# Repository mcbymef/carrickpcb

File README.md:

Contains Eagle projects for independent study PCB

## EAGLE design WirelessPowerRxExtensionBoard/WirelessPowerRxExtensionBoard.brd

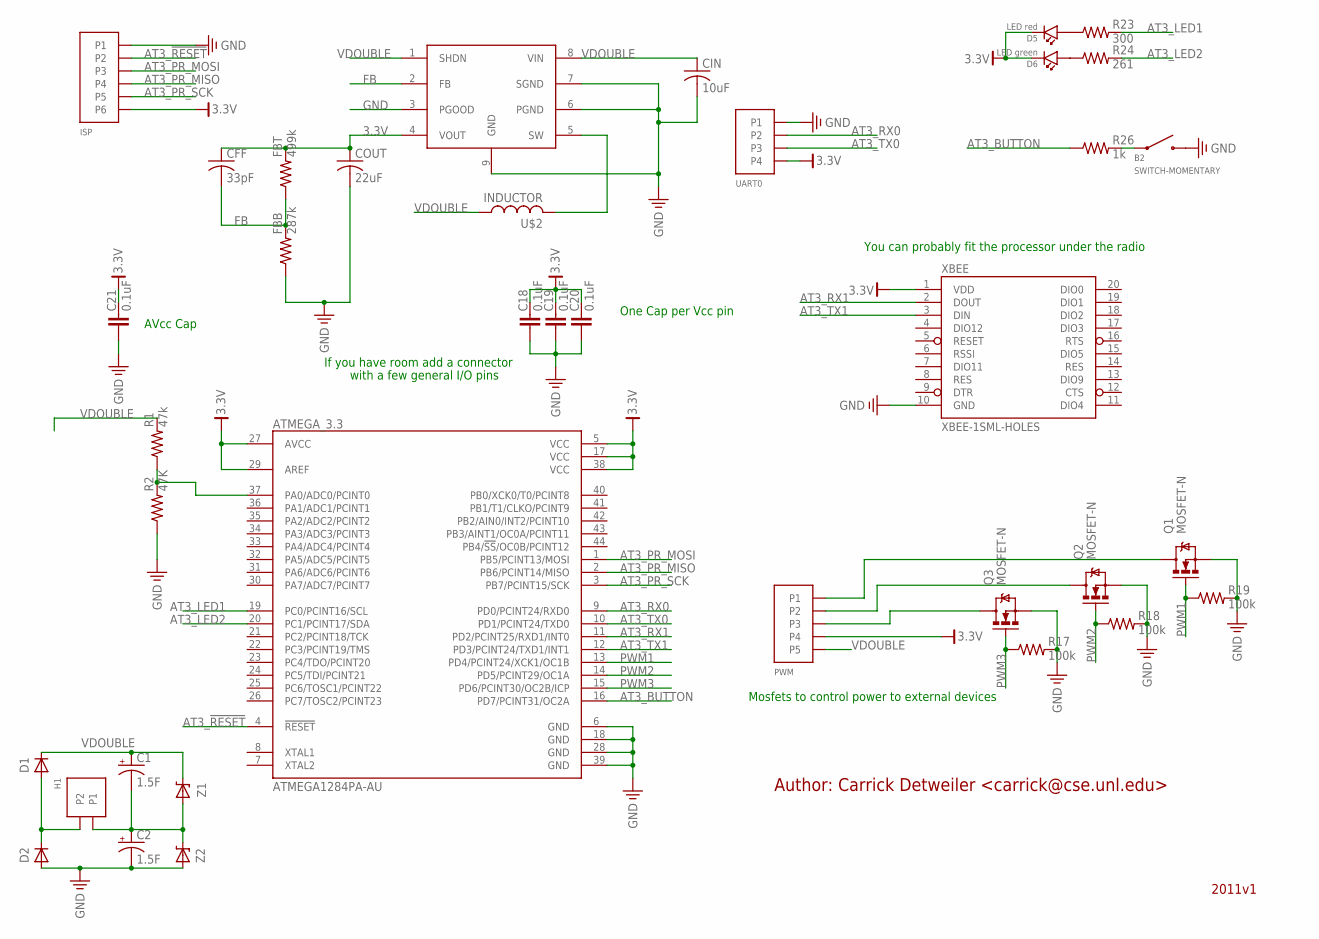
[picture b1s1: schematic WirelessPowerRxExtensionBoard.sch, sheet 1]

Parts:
ATMEGA_3.3: ATMEGA1284PA-AU; AT_TQFP-44
B2: SWITCH-MOMENTARY; SWITCH-MOMENTARY-PTS635-SMD
C1, C2: 1.5F; E5-10,5
C18, C19, C20, C21: 0.1uF; C0603
CFF: 33pF; C0201
CIN: 10uF; C0805
COUT: 22uF; C0805
D1, D2: DIODE; DO-214AB
D5: LED red; LED0603; DIGIKEY 160-1181-1-ND
D6: LED green; LED0603; DIGIKEY 160-1435-1-ND
FBB: 287k; R0603
FBT: 499k; R0603
H1: DF3-2
ISP: DF3-6
PWM: DF3-5
Q1, Q2, Q3: MOSFET-N; SOT-23
R1: 47k; R0603
R2: 47K; R0603
R17, R18, R19: 100k; R0603
R23: 300; R0603
R24: 261; R0603
R26: 1k; R0603
U$1: STEPUPCONVERTER; LTC3528/LTC3528B
U$2: INDUCTOR; WE-TPC-M
UART0: DF3-4
XBEE: XBEE-1SML-HOLES; XBEE-SML-HOLES
Z1, Z2: ZENERDIODE; SOD-123

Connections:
3.3V: ATMEGA_3.3.5 (VCC), ATMEGA_3.3.17 (VCC), ATMEGA_3.3.27 (AVCC), ATMEGA_3.3.29 (AREF), ATMEGA_3.3.38 (VCC), C18.P$2, C19.P$2, C20.P$2, C21.P$2, CFF.1, COUT.1, D5.P$2, D6.P$2, FBT.P$2 (2), ISP.P$6 (P6), PWM.P$4 (P4), U$1.4 (VOUT), UART0.P$4 (P4), XBEE.1 (VDD)
AT3_!RESET!: ATMEGA_3.3.4 (!RESET!), ISP.P$2 (P2)
AT3_BUTTON: ATMEGA_3.3.16 (PD7/PCINT31/OC2A), R26.P$1 (1)
AT3_LED1: ATMEGA_3.3.19 (PC0/PCINT16/SCL), R23.P$2 (2)
AT3_LED2: ATMEGA_3.3.20 (PC1/PCINT17/SDA), R24.P$2 (2)
AT3_PR_MISO: ATMEGA_3.3.2 (PB6/PCINT14/MISO), ISP.P$4 (P4)
AT3_PR_MOSI: ATMEGA_3.3.1 (PB5/PCINT13/MOSI), ISP.P$3 (P3)
AT3_PR_SCK: ATMEGA_3.3.3 (PB7/PCINT15/SCK), ISP.P$5 (P5)
AT3_RX0: ATMEGA_3.3.9 (PD0/PCINT24/RXD0), UART0.P$2 (P2)
AT3_RX1: ATMEGA_3.3.11 (PD2/PCINT25/RXD1/INT0), XBEE.2 (DOUT)
AT3_TX0: ATMEGA_3.3.10 (PD1/PCINT24/TXD0), UART0.P$3 (P3)
AT3_TX1: ATMEGA_3.3.12 (PD3/PCINT24/TXD1/INT1), XBEE.3 (DIN)
FB: CFF.2, FBB.P$2 (2), FBT.P$1 (1), U$1.2 (FB)
GND: ATMEGA_3.3.6 (GND), ATMEGA_3.3.18 (GND), ATMEGA_3.3.28 (GND), ATMEGA_3.3.39 (GND), B2.P$2, C2.-, C18.P$1, C19.P$1, C20.P$1, C21.P$1, CIN.2, COUT.2, D2.P$2 (A), FBB.P$1 (1), ISP.P$1 (P1), Q1.2 (S), Q2.2 (S), Q3.2 (S), R2.P$1 (1), R17.P$2 (2), R18.P$2 (2), R19.P$2 (2), U$1.3 (PGOOD), U$1.6 (PGND), U$1.7 (SGND), U$1.9 (GND), UART0.P$1 (P1), XBEE.10 (GND), Z2.P$2 (A)
unnamed: D1.P$2 (A), D2.P$1 (C), H1.P$2 (P2)
unnamed: ATMEGA_3.3.37 (PA0/ADC0/PCINT0), R1.P$1 (1), R2.P$2 (2)
unnamed: C1.-, C2.+, H1.P$1 (P1), Z1.P$2 (A), Z2.P$1 (C)
unnamed: PWM.P$3 (P3), Q3.3 (D)
unnamed: PWM.P$2 (P2), Q2.3 (D)
unnamed: B2.P$1, R26.P$2 (2)
unnamed: PWM.P$1 (P1), Q1.3 (D)
unnamed: D5.P$1, R23.P$1 (1)
unnamed: D6.P$1, R24.P$1 (1)
PWM1: ATMEGA_3.3.13 (PD4/PCINT24/XCK1/OC1B), Q1.1 (G), R19.P$1 (1)
PWM2: ATMEGA_3.3.14 (PD5/PCINT29/OC1A), Q2.1 (G), R18.P$1 (1)
PWM3: ATMEGA_3.3.15 (PD6/PCINT30/OC2B/ICP), Q3.1 (G), R17.P$1 (1)
SW: U$1.5 (SW), U$2.P$2 (2)
VDOUBLE: C1.+, CIN.1, D1.P$1 (C), PWM.P$5 (P5), R1.P$2 (2), U$1.1 (SHDN), U$1.8 (VIN), U$2.P$1 (1), Z1.P$1 (C)

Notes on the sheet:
Author: Carrick Detweiler <carrick@cse.unl.edu>
2011v1
One Cap per Vcc pin
AVcc Cap
If you have room add a connector
with a few general I/O pins
You can probably fit the processor under the radio
Mosfets to control power to external devices

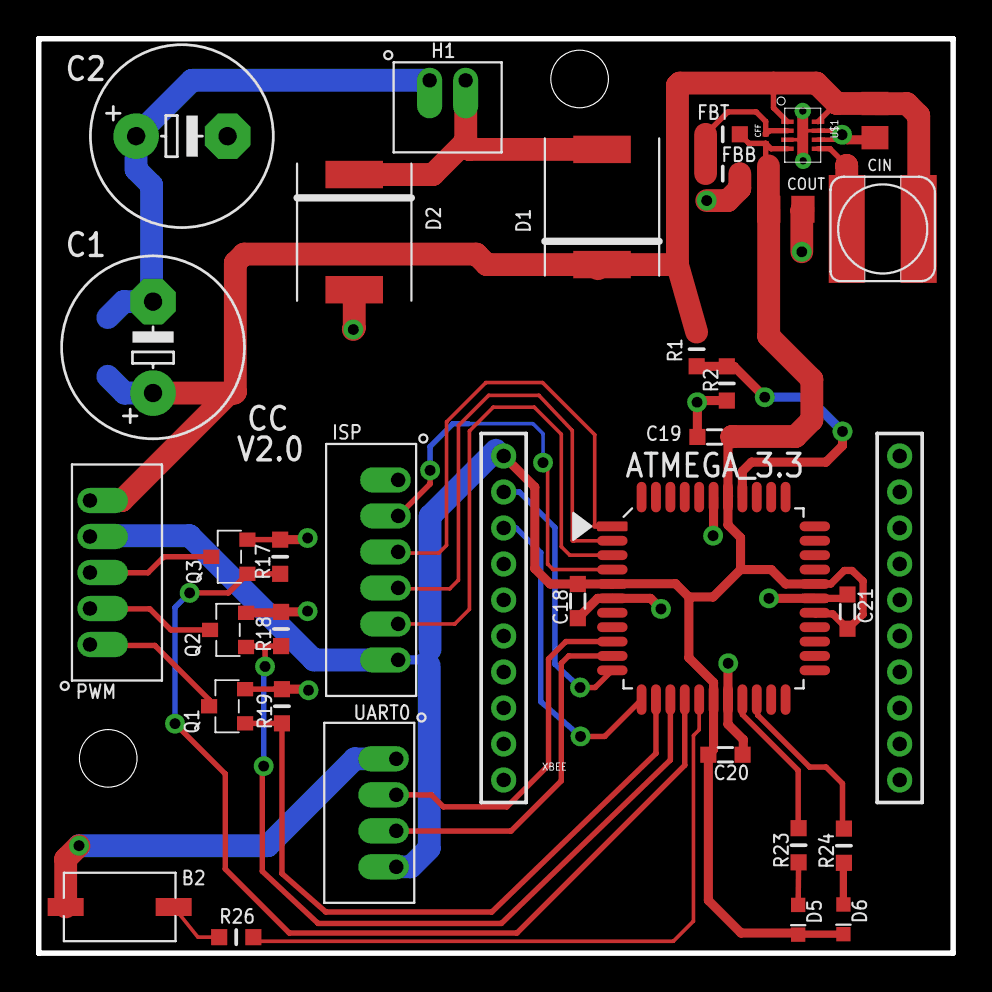
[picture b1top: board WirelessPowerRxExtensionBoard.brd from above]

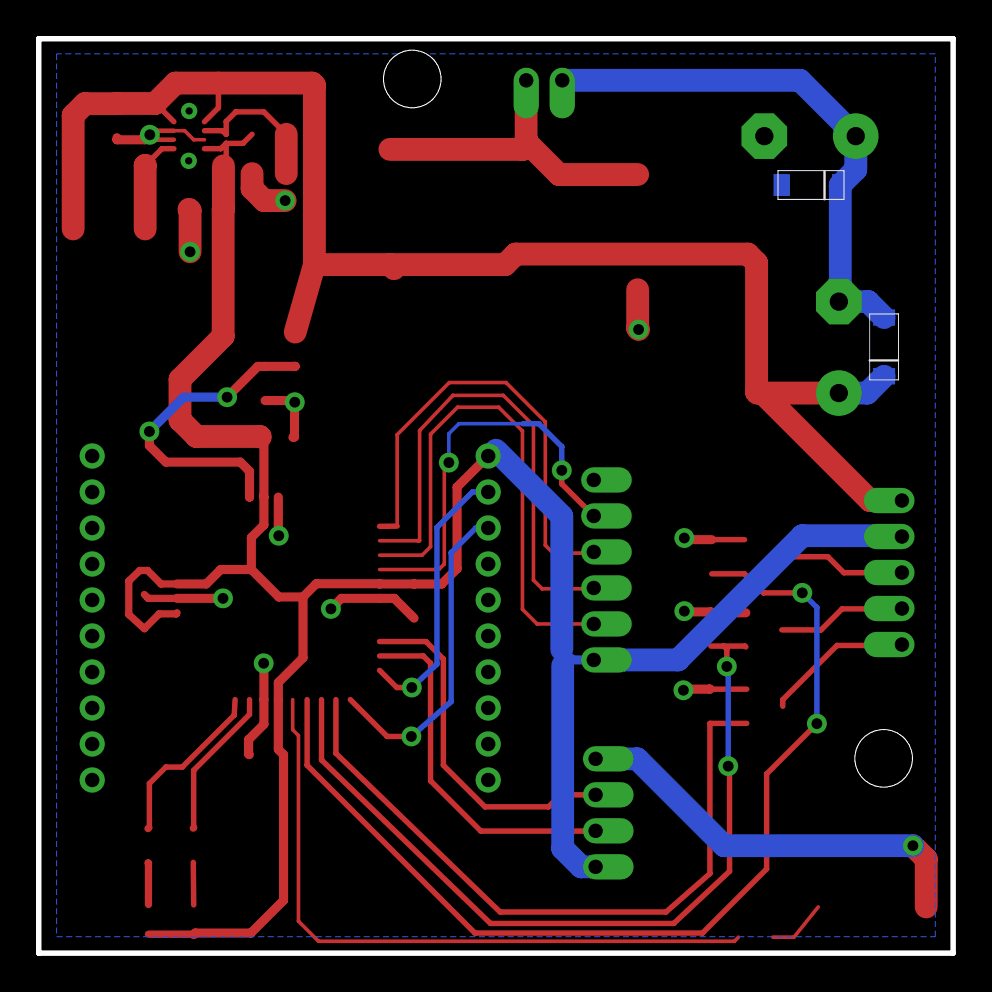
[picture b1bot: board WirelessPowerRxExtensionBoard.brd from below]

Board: 2 copper layers, 50.8 x 50.8 mm, 37 parts (2 on the bottom side), 28 nets.

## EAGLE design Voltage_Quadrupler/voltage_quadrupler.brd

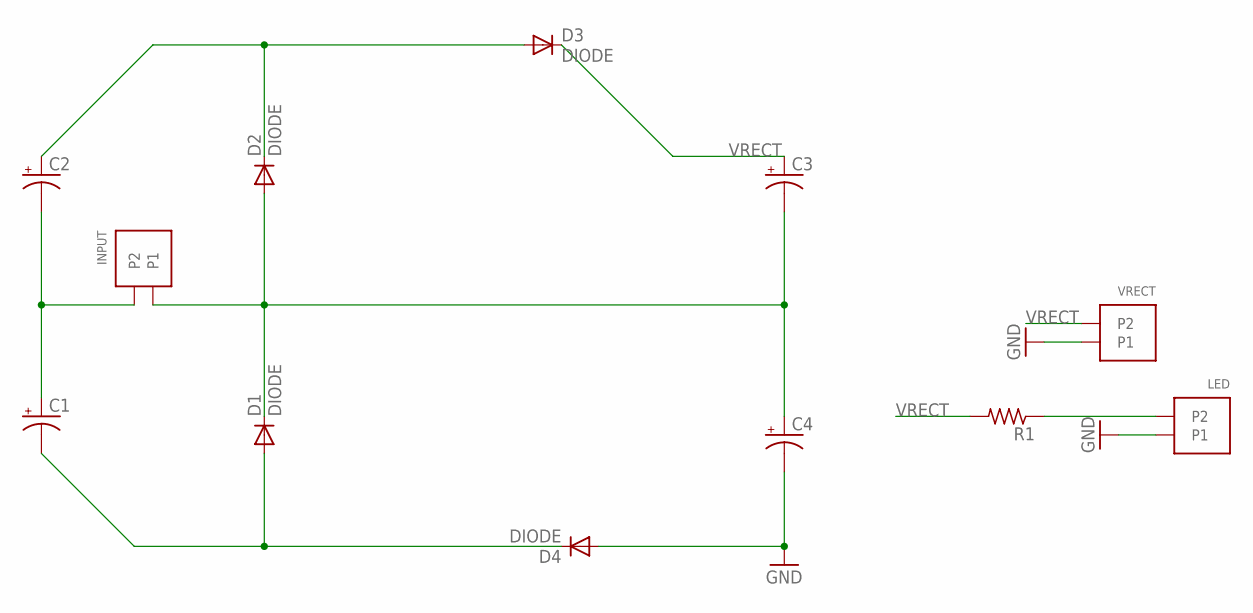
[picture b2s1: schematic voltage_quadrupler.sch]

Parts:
C1, C2, C3, C4: CPOL-USE7.5-18; E7,5-18
D1, D2, D3, D4: DIODE; DO-214AB
INPUT: DF3-2
LED: DF3-2
R1: R-US_0207/7; 0207/7
VRECT: DF3-2

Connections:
GND: C4.-, D4.P$2 (A), LED.P$1 (P1), VRECT.P$1 (P1)
unnamed: C3.-, C4.+, D1.P$1 (C), D2.P$2 (A), INPUT.P$1 (P1)
unnamed: C2.+, D2.P$1 (C), D3.P$2 (A)
unnamed: C1.+, C2.-, INPUT.P$2 (P2)
unnamed: C1.-, D1.P$2 (A), D4.P$1 (C)
unnamed: LED.P$2 (P2), R1.1
VRECT: C3.+, D3.P$1 (C), R1.2, VRECT.P$2 (P2)

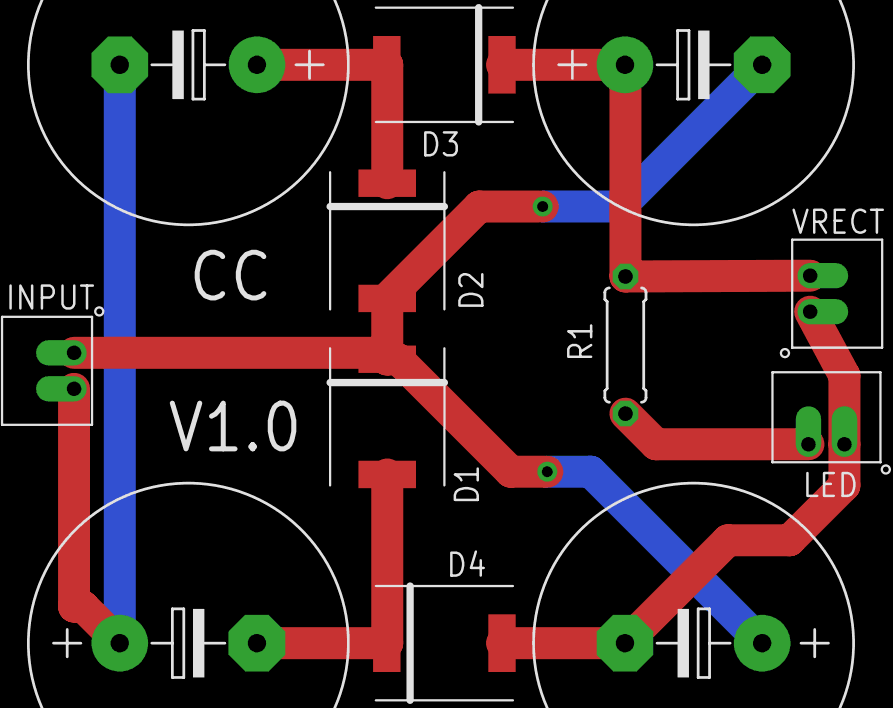
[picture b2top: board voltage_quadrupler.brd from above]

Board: 2 copper layers, 12 parts (0 on the bottom side), 7 nets.

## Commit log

2013-04-01 Adding Wireless Power Rx Extension Board Schematic
2013-04-03 Adding My Library
2013-04-03 Integrated MCU with Voltage Doubler and Regulator
    Board still needs to be routed, verify schematic with Carrick as well.
2013-04-05 Finished Schematic for Wireless Power Rx Extension Board
    Also updated crawford library to include zener diode
2013-04-07 Lots of Routing progress
    Routing!
2013-04-08 Finished First Pass at Routing
    still need to add vias to ground for voltage regulator
2013-04-10 Updated Routing
    Re-routed power section with much larger traces and added ground plane.
    Moved MCU resistors and caps under the radio but they still need to be
    re-routed.
2013-04-11 First Routing Revision Complete
    Much improved since the first routing!
2013-04-11 Second Rerouting Revision Complete
    Extended Ground plane across entire board, switched Voltage regulator
    feedback resistors to 0603

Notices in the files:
parts and their libraries:
SparkFun-Aesthetics: Licensing: CC v3.0 Share-Alike You are welcome to use this library for commercial purposes.
